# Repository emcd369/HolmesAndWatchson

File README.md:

# HolmesAndWatchson
Designing a Smartwatch

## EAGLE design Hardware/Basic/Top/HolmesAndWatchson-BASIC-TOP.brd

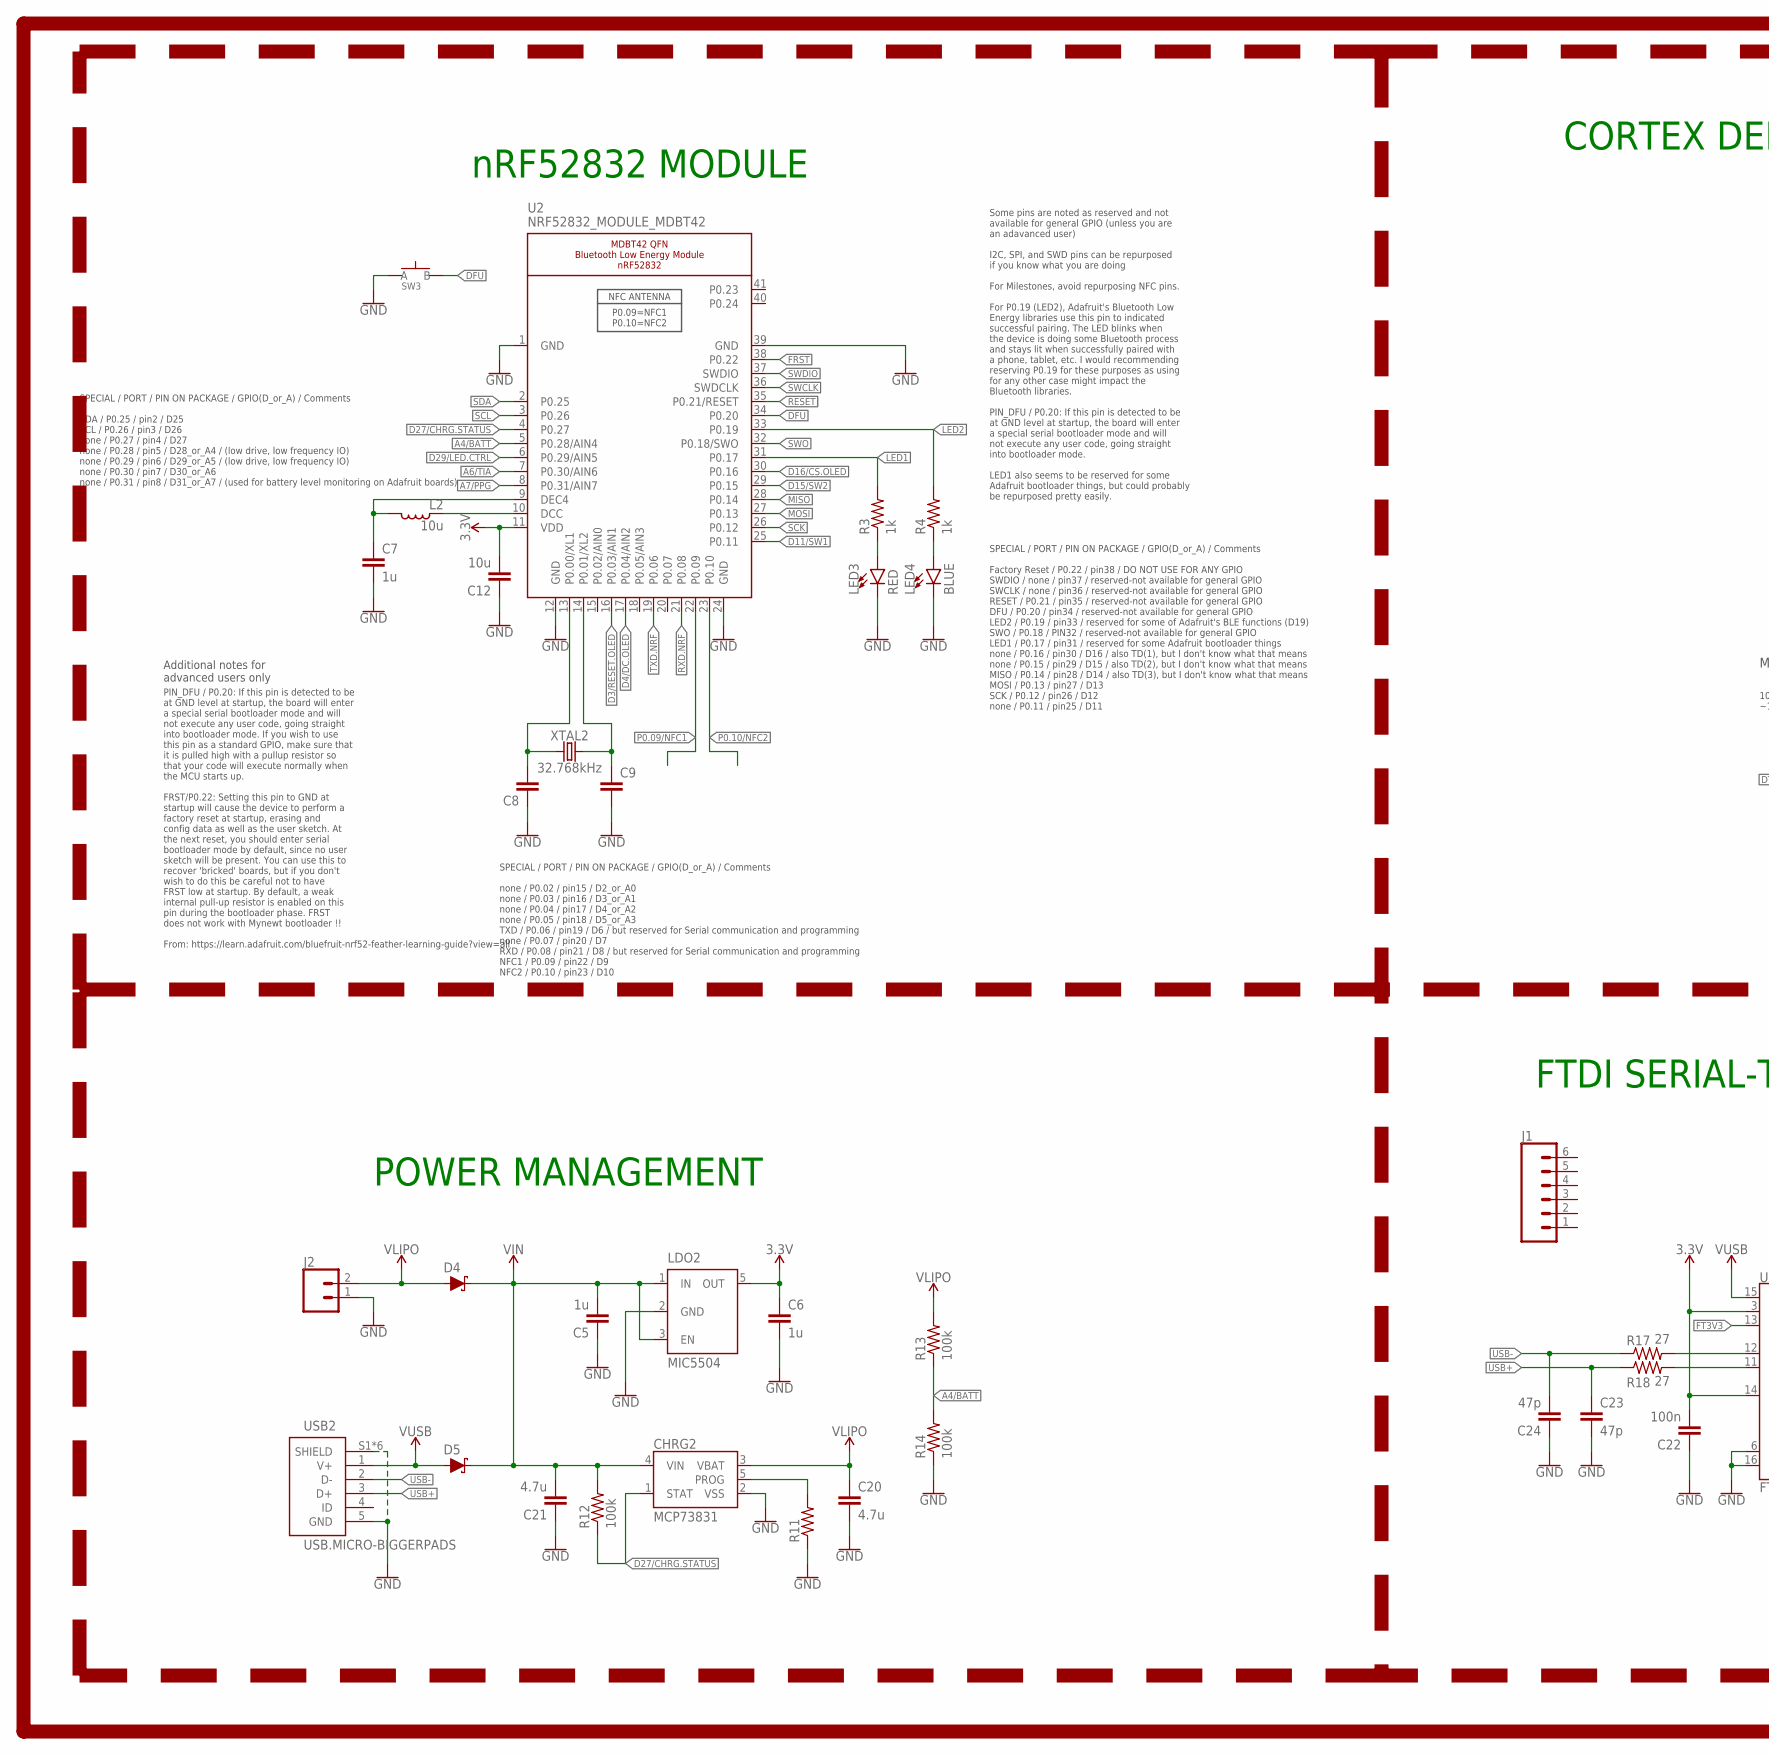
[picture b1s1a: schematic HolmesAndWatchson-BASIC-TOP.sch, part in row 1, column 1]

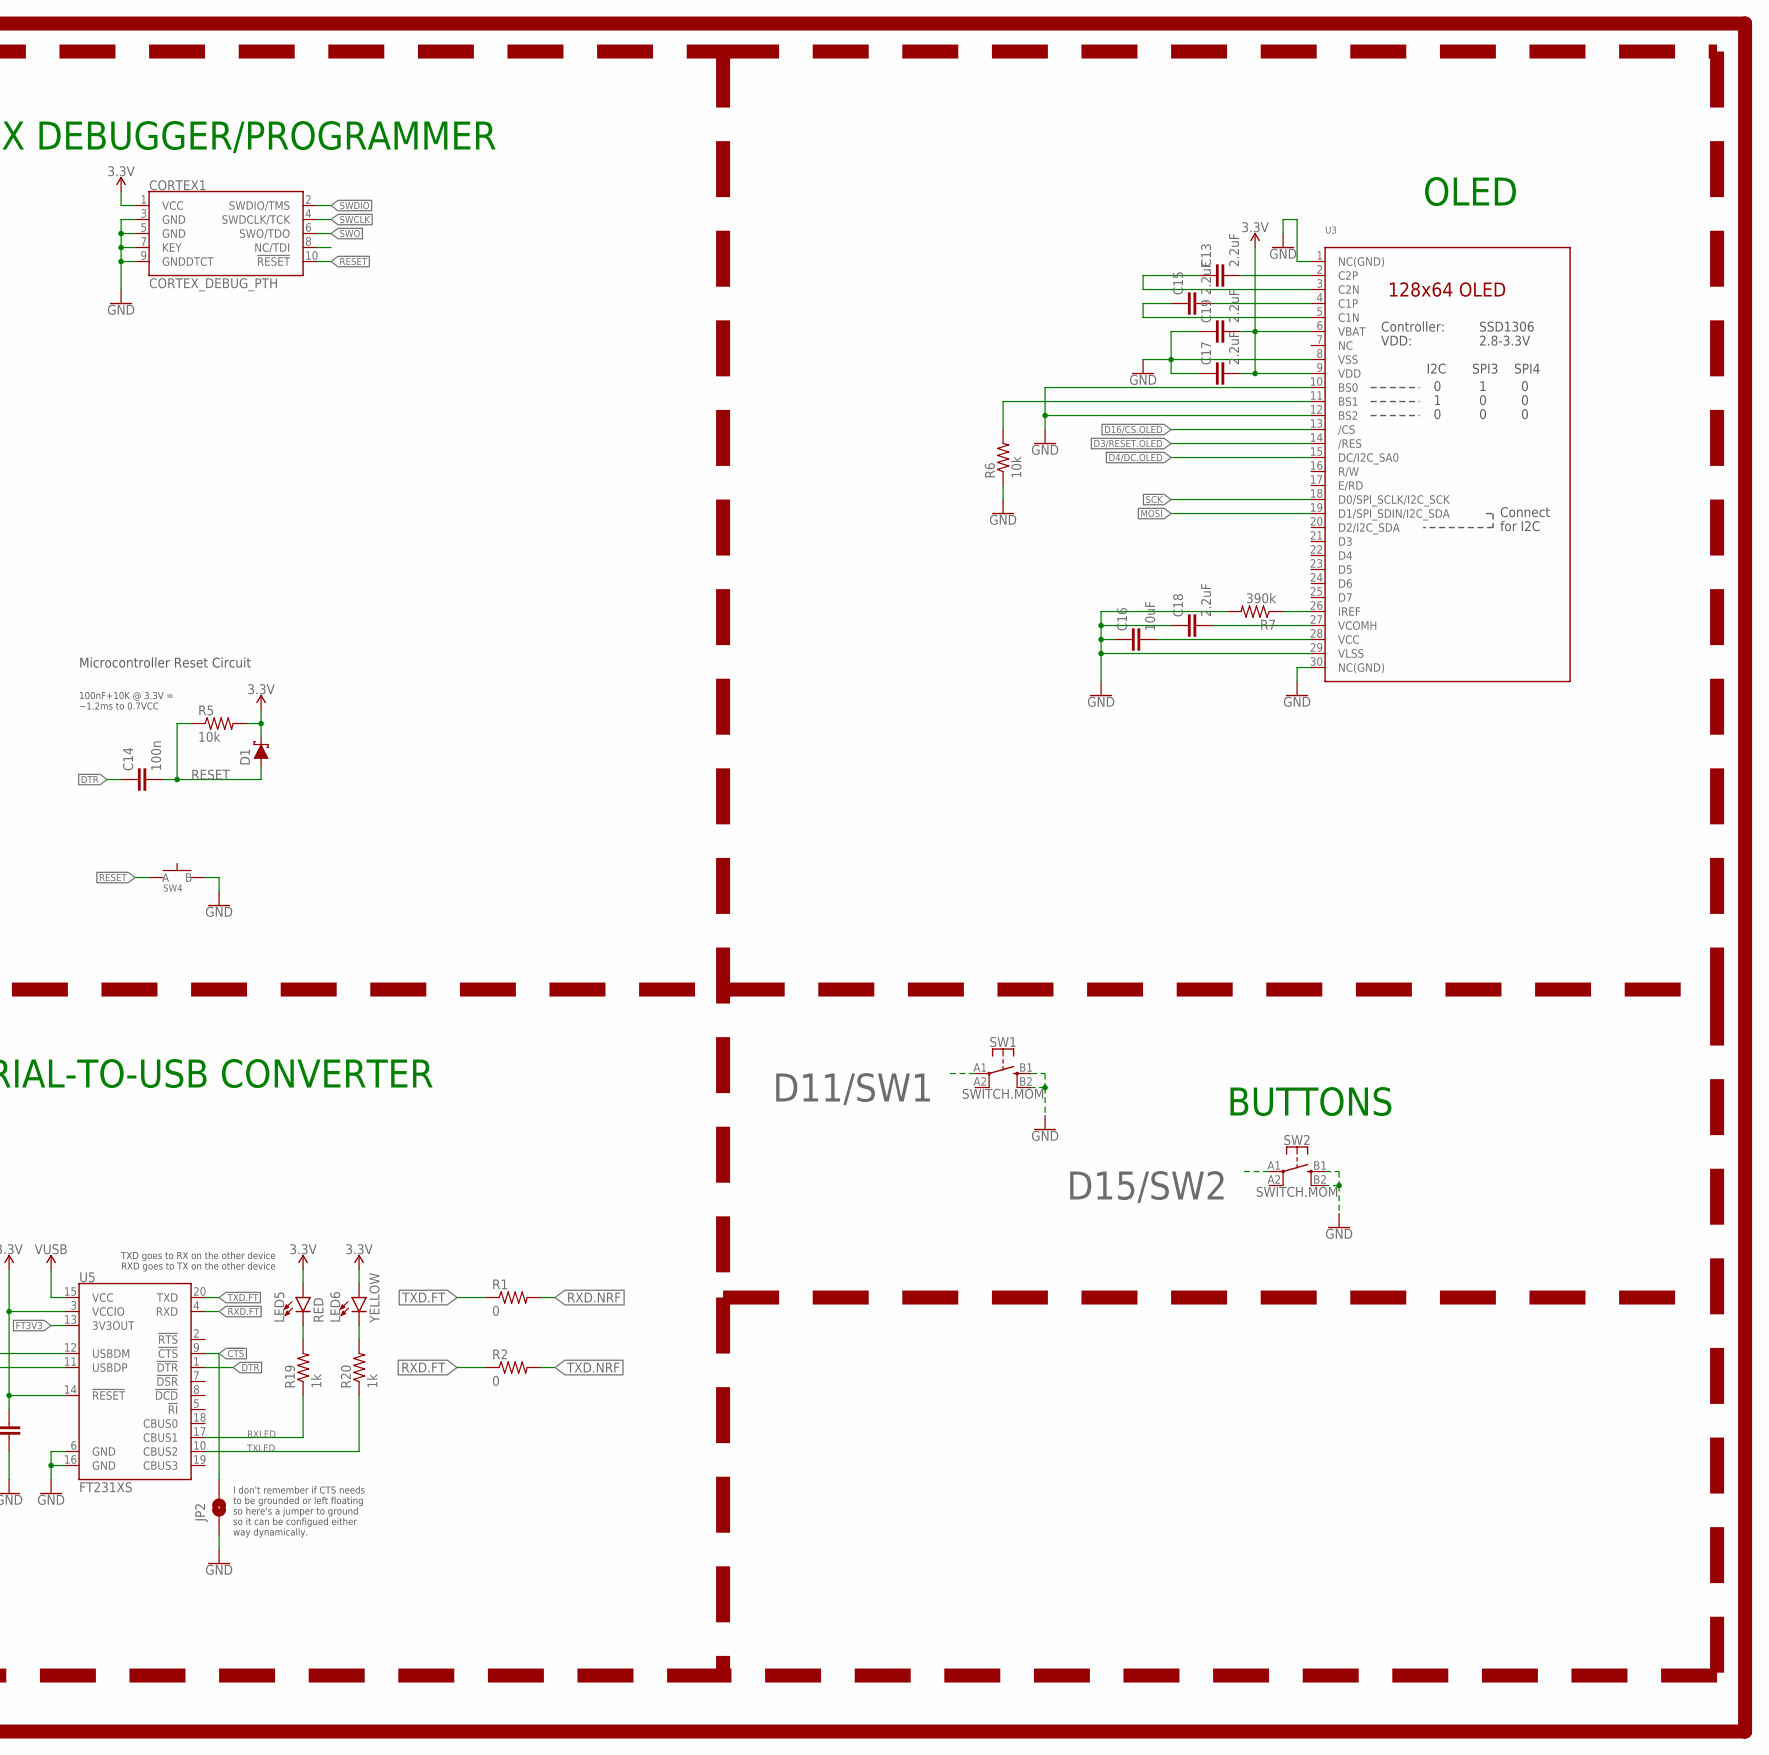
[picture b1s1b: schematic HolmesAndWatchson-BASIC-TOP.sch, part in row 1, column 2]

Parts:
C5, C6, C7: 1u; C0603
C8, C9: CAPACITOR0603; C0603
C12: 10u; C0805
C13, C15, C17, C18, C19: 2.2uF; C0402
C14, C22: 100n; C0603
C16: 10uF; C0603
C20, C21: 4.7u; C0603
C23, C24: 47p; C0603
CHRG2: MCP73831; SOT23-5
CORTEX1: CORTEX_DEBUG_PTH; 2X5-PTH-1.27MM
D1, D4, D5: SCHOTTKY-USC; USC
J1: CONN_061.27MM; 1X06_1.27MM
J2: CONN_02; 1X02
JP2: JUMPER-SMT_2_NO_SILK; SMT-JUMPER_2_NO_SILK
L2: 10u; L0603
LDO2: MIC5504; SOT23-5
LED3, LED5: RED; LED-0603
LED4: BLUE; LED-0603
LED6: YELLOW; LED-0603
R1, R2: 0; R0603
R3, R4, R19, R20: 1k; R0603
R5, R6: 10k; R0603
R7: 390k; R0603
R11: RESISTOR0603; R0603
R12, R13, R14: 100k; R0603
R17, R18: 27; R0603
SW1, SW2: SWITCH.MOM; TACTILE_SWITCH_SMD_6.2MM_TALL
SW3, SW4: SPST-PTS830GG140-COPY.1-3; BUTTON-GULLWING
U2: NRF52832_MODULE_MDBT42; BLE_MODULE_RAYTAC_MDBT42
U3: DISP_OLED_UG-2864HSWEG01-NO-WRAPAROUND; UG-2864HSWEG01_0.96IN_NO-WRAPAROUND
U5: FT231XS; SSOP20_L
USB2: USB.MICRO-BIGGERPADS; USB-MICRO-01.BIGGERPADS
XTAL2: 32.768kHz; 2-SMD.NOLEAD.2.0MMTO1.2MM

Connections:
3.3V: C6.1, C12.2, C17.2, C19.2, C22.2, CORTEX1.1 (VCC), D1.- (C), LDO2.5 (OUT), LED5.A, LED6.A, R5.2, U2.11 (VDD), U3.6 (VBAT), U3.9 (VDD), U5.3 (VCCIO), U5.14 (!RESET)
!CTS: JP2.2, U5.9 (!CTS)
A4/BATT: R13.1, R14.2, U2.5 (P0.28/AIN4)
A6/TIA: U2.7 (P0.30/AIN6)
A7/PPG: U2.8 (P0.31/AIN7)
D3/RESET.OLED: U2.16 (P0.03/AIN1), U3.14 (/RES)
D4/DC.OLED: U2.17 (P0.04/AIN2), U3.15 (DC/I2C_SA0)
D11/SW1: SW1.A1 (1), U2.25 (P0.11)
D15/SW2: SW2.A1 (1), U2.29 (P0.15)
D16/CS.OLED: U2.30 (P0.16), U3.13 (/CS)
D27/CHRG.STATUS: CHRG2.1 (STAT), R12.1, U2.4 (P0.27)
D29/LED.CTRL: U2.6 (P0.29/AIN5)
DFU: SW3.3 (B), U2.34 (P0.20)
DTR: C14.1, U5.1 (!DTR)
FRST: U2.38 (P0.22)
FT3V3: U5.13 (3V3OUT)
GND: C5.1, C6.2, C7.2, C8.1, C9.2, C12.1, C16.1, C17.1, C18.1, C19.1, C20.2, C21.1, C22.1, C23.2, C24.1, CHRG2.2 (VSS), CORTEX1.3 (GND), CORTEX1.5 (GND), CORTEX1.7 (KEY), CORTEX1.9 (GNDDTCT), J2.1, JP2.1, LDO2.2 (GND), LED3.C, LED4.C, R6.1, R7.2, R11.1, R14.1, SW1.B1 (3), SW1.B2 (4), SW2.B1 (3), SW2.B2 (4), SW3.1 (A), SW4.3 (B), U2.1 (GND), U2.12 (GND), U2.24 (GND), U2.39 (GND), U3.1 (NC(GND)), U3.8 (VSS), U3.10 (BS0), U3.12 (BS2), U3.29 (VLSS), U3.30 (NC(GND)), U5.6 (GND), U5.16 (GND), USB2.5 (GND), USB2.S1 (SHIELD), USB2.S2 (SHIELD), USB2.S3 (SHIELD), USB2.S4 (SHIELD), USB2.S5 (SHIELD), USB2.S6 (SHIELD)
LED1: R3.2, U2.31 (P0.17)
LED2: R4.2, U2.33 (P0.19)
MISO: U2.28 (P0.14)
MOSI: U2.27 (P0.13), U3.19 (D1/SPI_SDIN/I2C_SDA)
unnamed: R6.2, U3.11 (BS1)
unnamed: R7.1, U3.26 (IREF)
unnamed: C13.2, U3.2 (C2P)
unnamed: C8.2, U2.13 (P0.00/XL1), XTAL2.P$1 (1)
unnamed: C13.1, U3.3 (C2N)
unnamed: C9.1, U2.14 (P0.01/XL2), XTAL2.P$2 (2)
unnamed: C15.2, U3.4 (C1P)
unnamed: C15.1, U3.5 (C1N)
unnamed: LED3.A, R3.1
unnamed: LED4.A, R4.1
unnamed: L2.1, U2.10 (DCC)
unnamed: C7.1, L2.2, U2.9 (DEC4)
unnamed: C16.2, U3.28 (VCC)
unnamed: C18.2, U3.27 (VCOMH)
unnamed: CHRG2.5 (PROG), R11.2
unnamed: R17.2, U5.12 (USBDM)
unnamed: R18.2, U5.11 (USBDP)
unnamed: LED5.C, R19.2
unnamed: LED6.C, R20.2
P0.09/NFC1: U2.22 (P0.09)
P0.10/NFC2: U2.23 (P0.10)
RESET: C14.2, CORTEX1.10 (!RESET), D1.+ (A), R5.1, SW4.1 (A), U2.35 (P0.21/RESET)
RXD.FT: R2.1, U5.4 (RXD)
RXD.NRF: R1.2, U2.21 (P0.08)
RXLED: R19.1, U5.17 (CBUS1)
SCK: U2.26 (P0.12), U3.18 (D0/SPI_SCLK/I2C_SCK)
SCL: U2.3 (P0.26)
SDA: U2.2 (P0.25)
SWCLK: CORTEX1.4 (SWDCLK/TCK), U2.36 (SWDCLK)
SWDIO: CORTEX1.2 (SWDIO/TMS), U2.37 (SWDIO)
SWO: CORTEX1.6 (SWO/TDO), U2.32 (P0.18/SWO)
TXD.FT: R1.1, U5.20 (TXD)
TXD.NRF: R2.2, U2.19 (P0.06)
TXLED: R20.1, U5.10 (CBUS2)
USB+: C23.1, R18.1, USB2.3 (D+)
USB-: C24.2, R17.1, USB2.2 (D-)
VIN: C5.2, C21.2, CHRG2.4 (VIN), D4.- (C), D5.- (C), LDO2.1 (IN), LDO2.3 (EN), R12.2
VLIPO: C20.1, CHRG2.3 (VBAT), D4.+ (A), J2.2, R13.2
V_USB: D5.+ (A), U5.15 (VCC), USB2.1 (V+)

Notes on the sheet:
Microcontroller Reset Circuit
100nF+10K @ 3.3V = ~1.2ms to 0.7VCC
SPECIAL / PORT / PIN ON PACKAGE / GPIO(D_or_A) / Comments SDA / P0.25 / pin2 / D25 SCL / P0.26 / pin3 / D26 none / P0.27 / pin4 / D27 none / P0.28 / pin5 / D28_or_A4 / (low drive, low frequency IO) none / P0.29 / pin6 / D29_or_A5 / (low drive, low frequency IO) none / P0.30 / pin7 / D30_or_A6 none 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
SPECIAL / PORT / PIN ON PACKAGE / GPIO(D_or_A) / Comments none / P0.02 / pin15 / D2_or_A0 none / P0.03 / pin16 / D3_or_A1 none / P0.04 / pin17 / D4_or_A2 none / P0.05 / pin18 / D5_or_A3 TXD / P0.06 / pin19 / D6 / but reserved for Serial communication and programming none / P0.07 / pin20 / D7 RXD / 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
SPECIAL / PORT / PIN ON PACKAGE / GPIO(D_or_A) / Comments Factory Reset / P0.22 / pin38 / DO NOT USE FOR ANY GPIO SWDIO / none / pin37 / reserved-not available for general GPIO SWCLK / none / pin36 / reserved-not available for general GPIO RESET / P0.21 / pin35 / reserved-not available for general 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
Some pins are noted as reserved and not available for general GPIO (unless you are an adavanced user) I2C, SPI, and SWD pins can be repurposed if you know what you are doing For Milestones, avoid repurposing NFC pins. For P0.19 (LED2), Adafruit's Bluetooth Low Energy libraries use this pin to indic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
PIN_DFU / P0.20: If this pin is detected to be at GND level at startup, the board will enter a special serial bootloader mode and will not execute any user code, going straight into bootloader mode. If you wish to use this pin as a standard GPIO, make sure that it is pulled high with a pullup resis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
Additional notes for advanced users only
BUTTONS
OLED
nRF52832 MODULE
CORTEX DEBUGGER/PROGRAMMER
POWER MANAGEMENT
TXD goes to RX on the other device RXD goes to TX on the other device
I don't remember if CTS needs to be grounded or left floating so here's a jumper to ground so it can be configued either way dynamically.
FTDI SERIAL-TO-USB CONVERTER

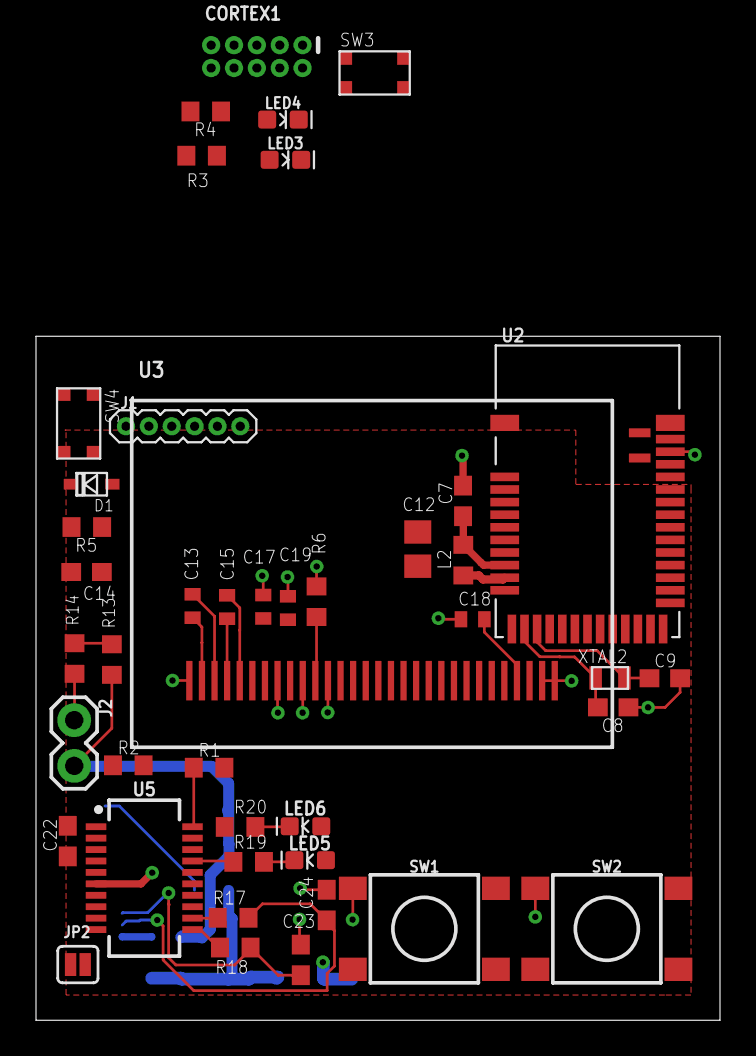
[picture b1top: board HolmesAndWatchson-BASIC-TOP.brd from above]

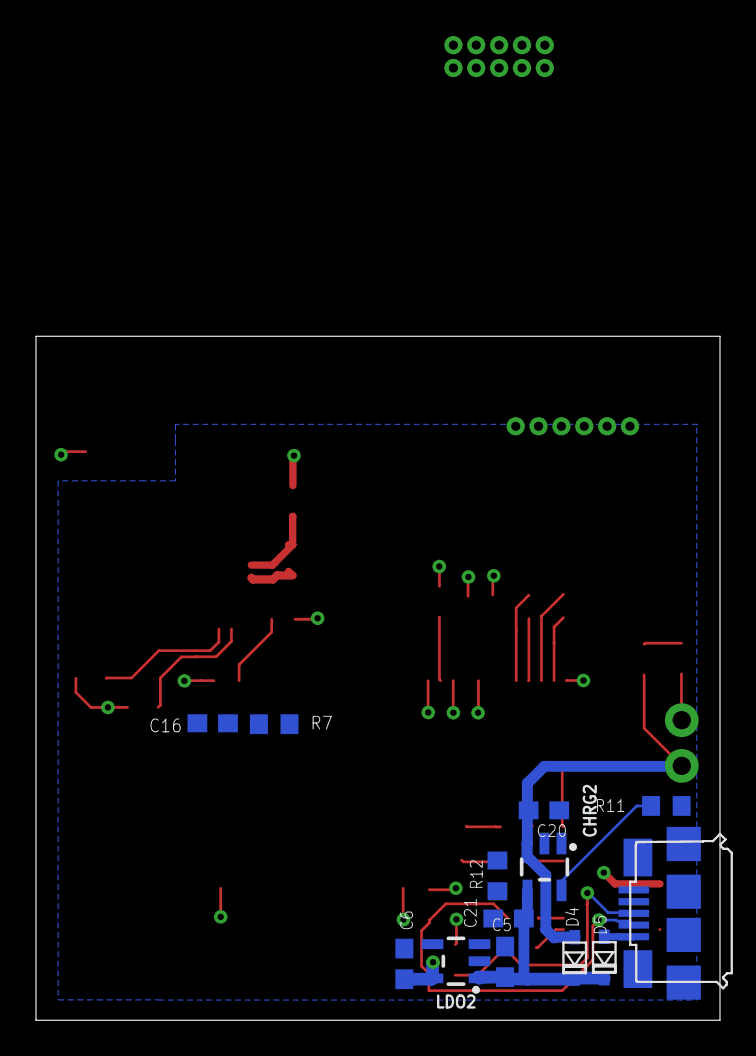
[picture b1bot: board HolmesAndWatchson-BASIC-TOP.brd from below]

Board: 2 copper layers, 38.0 x 38.0 mm, 56 parts (13 on the bottom side), 50 nets.

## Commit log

2020-06-30 features list
2020-07-01 Firmware and Hardware Folders
2020-07-11 top board rev1
2020-07-15 Take002 and top board schematic complete
2020-07-22 middle of take004 - routing TOP board
2020-07-29 OLED routing
2020-08-11 continue editing top board
2020-08-12 finished take 005
